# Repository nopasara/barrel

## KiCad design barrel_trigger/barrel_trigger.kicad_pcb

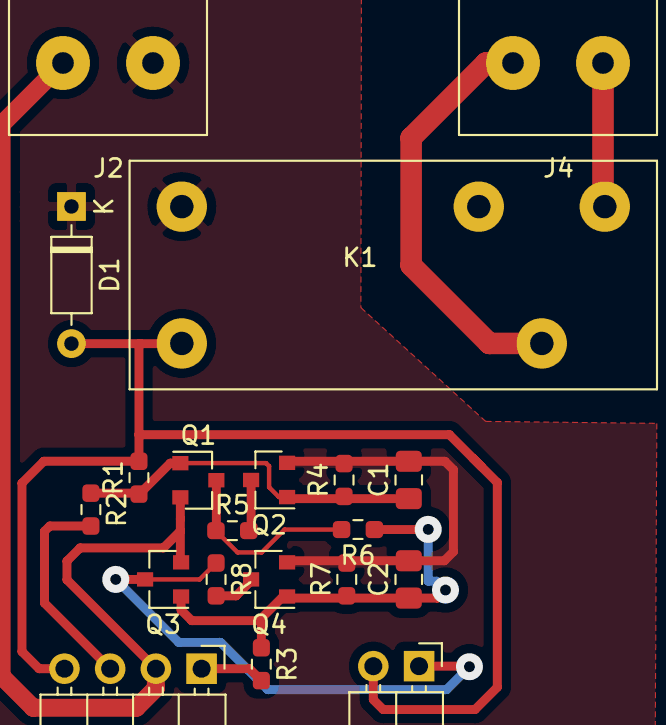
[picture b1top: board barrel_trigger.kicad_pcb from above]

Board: 2 copper layers, 20 parts (0 on the bottom side), 13 nets.

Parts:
C1, C2: 10nF; C_0805_2012Metric_Pad1.18x1.45mm_HandSolder
D1: DIODE; D_DO-35_SOD27_P7.62mm_Horizontal
J1: Conn_01x04_Male; PinHeader_1x04_P2.54mm_Horizontal
J2, J4: Conn_01x02_Male; connector_housing_5.0mm_1.2mm
J3: Conn_01x02_Male; PinHeader_1x02_P2.54mm_Horizontal
K1: DIPxx-1Cxx-51x; 845HN-1C-C
Q1, Q3: Q_PMOS_GSD; SOT-23
Q2, Q4: Q_NMOS_GSD; SOT-23
R1, R6: 100k; R_0603_1608Metric_Pad0.98x0.95mm_HandSolder
R2, R3, R5, R8: 10k; R_0603_1608Metric_Pad0.98x0.95mm_HandSolder
R4, R7: 680k; R_0603_1608Metric_Pad0.98x0.95mm_HandSolder

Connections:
12V: J1.2, J2.2, Q1.2, Q3.2
GND: C1.2, C2.2, D1.1, J2.1, K1.2, Q2.2, Q4.2, R4.2, R7.2
unnamed: C1.1, Q1.1, Q2.1, R1.1, R2.1, R4.1
unnamed: C2.1, Q3.1, Q4.1, R3.1, R6.1, R7.1
unnamed: D1.2, J1.4, J3.2, K1.6, R1.2
unnamed: J1.1, R3.2
unnamed: J1.3, R2.2
unnamed: J3.1, Q3.3, R8.1
unnamed: J4.1, K1.14
unnamed: J4.2, K1.7
unnamed: Q1.3, R5.1, R6.2
unnamed: Q2.3, R5.2
unnamed: Q4.3, R8.2

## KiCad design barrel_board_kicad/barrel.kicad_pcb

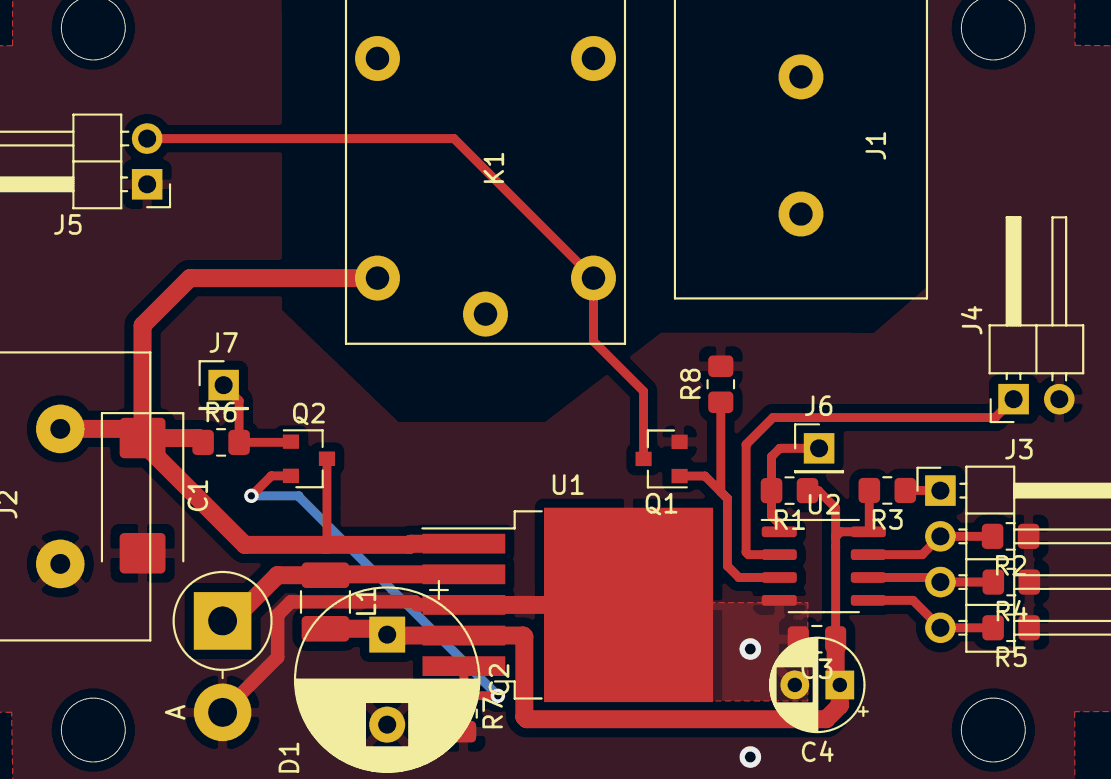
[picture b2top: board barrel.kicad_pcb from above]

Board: 2 copper layers, 26 parts (0 on the bottom side), 16 nets.

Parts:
C1: 100uF; CP_EIA-7343-31_Kemet-D_Pad2.25x2.55mm_HandSolder
C2: 1000uF; CP_Radial_D10.0mm_P5.00mm
C3: 100nF; C_0805_2012Metric_Pad1.18x1.45mm_HandSolder
C4: 10uF; CP_Radial_D5.0mm_P2.50mm
D1: 1N5822; D_DO-201AD_P5.08mm_Vertical_AnodeUp
J1: 220V; FB25C-B-02P
J2: 12V; dg128v-02
J3: probe/prog; PinHeader_1x04_P2.54mm_Horizontal
J4: valve; PinHeader_1x02_P2.54mm_Horizontal
J5: Bypass; PinHeader_1x02_P2.54mm_Horizontal
J6: reset; PinHeader_1x01_P2.54mm_Vertical
J7: emergency off; PinHeader_1x01_P2.54mm_Vertical
K1: DIPxx-1Cxx-51x; HLS8L--12DC-S-C
L1: 100uH; L_1210_3225Metric_Pad1.42x2.65mm_HandSolder
Q1: Q_NPN_BEC; SOT-23
Q2: Q_PNP_BCE; SOT-23
R1, R2, R4, R5, R6, R8: 10k; R_0805_2012Metric_Pad1.20x1.40mm_HandSolder
R3: 1k; R_0805_2012Metric_Pad1.20x1.40mm_HandSolder
R7: 47k; R_0805_2012Metric_Pad1.20x1.40mm_HandSolder
U1: LM2576S-5; TO-263-5_TabPin3
U2: ATtiny13A-SSU; SOIC-8_3.9x4.9mm_P1.27mm

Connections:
5V: J3.1, R3.1
12v: C1.1, J2.1, K1.6, Q2.3, R6.1, U1.1
GARDEN: J3.4, R5.2, U2.5
LOWER: J3.3, R4.2, U2.6
unnamed: C2.1, C3.1, C4.1, L1.2, R1.1, R3.2, U1.4, U2.8
unnamed: J1.1, K1.7
unnamed: J1.2, K1.14
unnamed: J4.1, U2.2
unnamed: J5.2, K1.2, Q1.3
unnamed: J7.1, Q2.1, R6.2
unnamed: Q1.1, R8.1, U2.3
unnamed: Q2.2, R7.1, U1.5
RESET: J6.1, R1.2, U2.1
UPPER: J3.2, R2.2, U2.7
gnd: C1.2, C2.2, C3.2, C4.2, D1.2, J2.2, J4.2, J5.1, Q1.2, R2.1, R4.1, R5.1, R7.2, R8.2, U1.3, U2.4
out: D1.1, L1.1, U1.2

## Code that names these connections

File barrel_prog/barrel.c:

#include <avr/sleep.h>
#include <avr/power.h>
#include <avr/interrupt.h>

#define GARDEN_PIN      (1 << PINB0)
#define LOWER_PIN       (1 << PINB1)
#define UPPER_PIN       (1 << PINB2)
#define VALVE_PIN       (1 << PINB3)
#define MOTOR_PIN       (1 << PINB4)
#define OUT_PINS        ((1 << DDB3) | (1 << DDB4))
/* Enable pin change interrupt for input pins: 0, 1, 2 */
#define PIN_INT_MASK    ((1 << PCINT0) | (1 << PCINT1) | (1 << PCINT2))

register unsigned char motor_enabled asm("r16");
register unsigned char prev_state asm("r17");

void main()
{
    motor_enabled = 0;
    prev_state = 0;
    cli();
    /* disable clock on ADC and counters */
    power_all_disable();
    /* Set deep sleep mode */
    set_sleep_mode(SLEEP_MODE_PWR_DOWN);
    sleep_enable();

    DDRB = OUT_PINS;
    PORTB = 0;
    GIMSK |= (1 << PCIE);
    PCMSK |= PIN_INT_MASK;

    sei();
    while(1) {
        sleep_cpu();
    };
}

ISR(PCINT0_vect)
{
    register unsigned char state = PINB;
    unsigned char pin_change = state ^ prev_state;

    PORTB |= VALVE_PIN;

    if (state & GARDEN_PIN) {
        if (pin_change & GARDEN_PIN) {
            motor_enabled = 1;
            PORTB |= (VALVE_PIN) | (MOTOR_PIN);
        }
    } else {
        register unsigned char tmp_port = PORTB & ~(VALVE_PIN);

        if (motor_enabled && (state & UPPER_PIN)) {
            motor_enabled = 0;
            tmp_port &= ~(MOTOR_PIN);
        } else if (!motor_enabled && (state & LOWER_PIN)) {
            motor_enabled = 1;
            tmp_port |= (MOTOR_PIN);
        }
        PORTB = tmp_port;
    }
    prev_state = state;
}

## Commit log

2021-08-06 Initial barrel project commit
    The project of the MCU controlling the water level in the barrel
    The project contains the KiCad project with the schemas and the
    firmware for the ATtyny13a MCU
2021-08-14 Optimize the scheme
    Remove redundant transistors
2021-08-15 Fix defines
    Fix the valve pin definition and add constants fo pin setup
2021-08-15 Fix relay scheme
    Add a resistor for the transistor that controlls relay to be in a defined state at startup
2022-01-29 Add barrel trigger schematics
    Add a simple RS trigger schematics
